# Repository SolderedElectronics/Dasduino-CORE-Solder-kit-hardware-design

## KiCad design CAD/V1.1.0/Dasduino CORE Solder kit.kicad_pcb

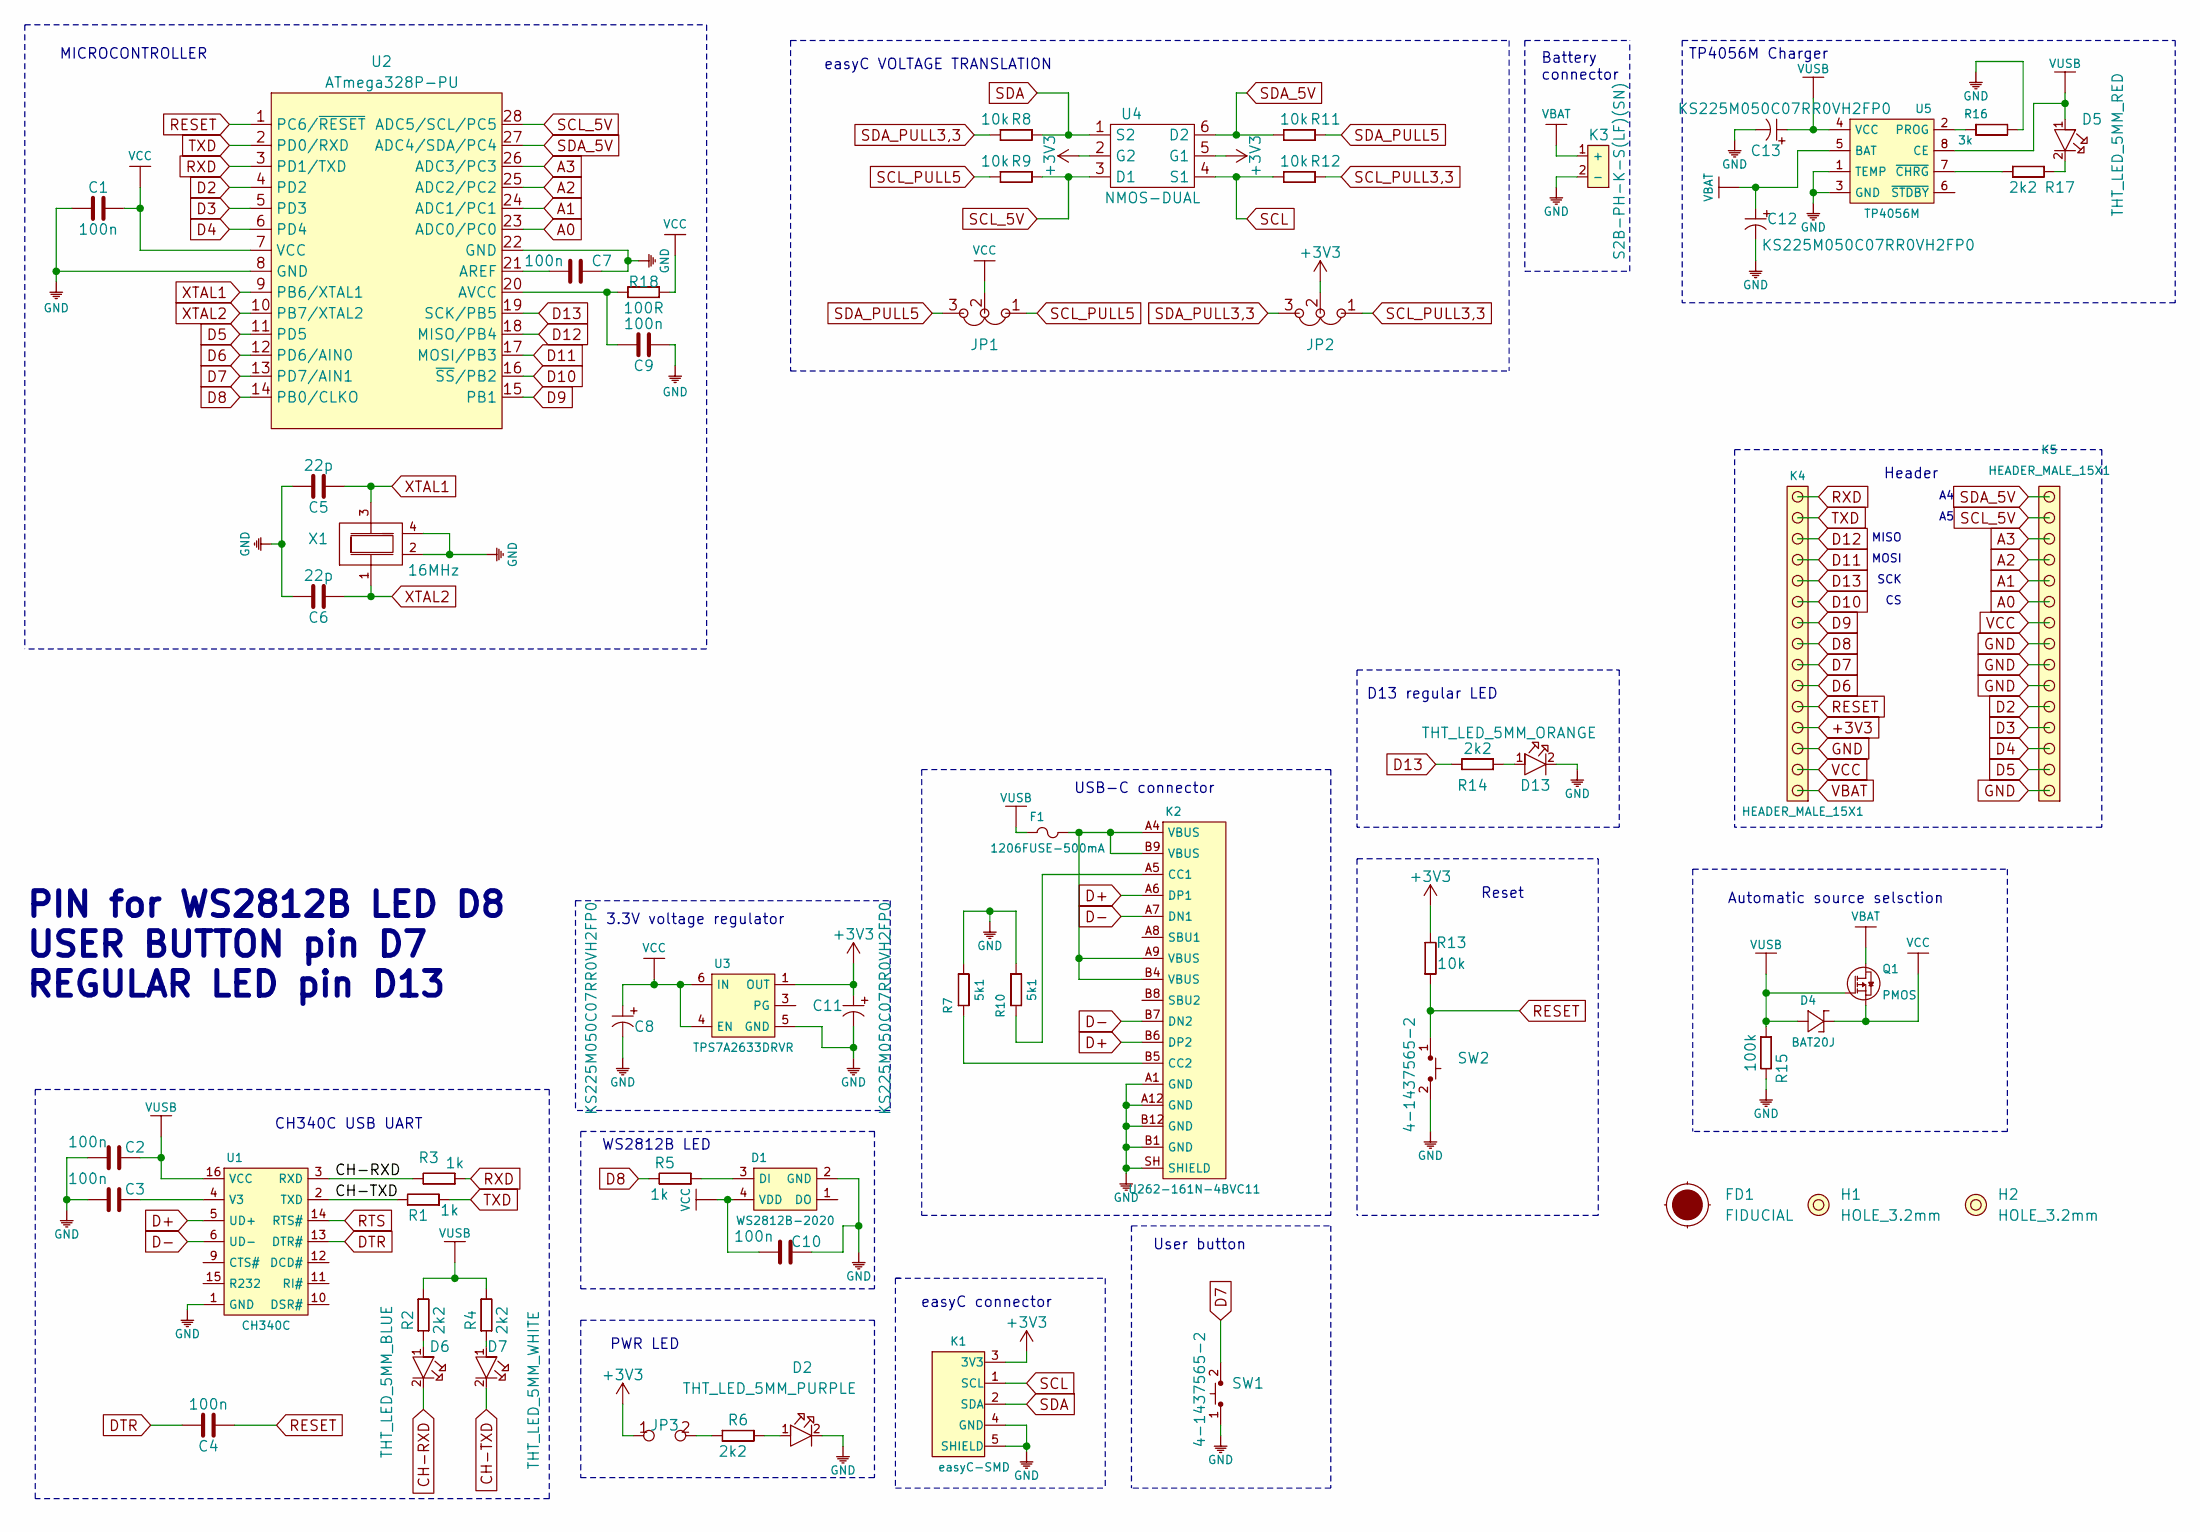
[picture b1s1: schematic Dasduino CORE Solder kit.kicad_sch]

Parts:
C1, C2, C3, C4, C7, C9, C10: 100n; C_Ceramic_THT_5mm
C5, C6: 22p; C_Ceramic_THT_5mm
C8, C11, C12, C13: KS225M050C07RR0VH2FP0
D1: WS2812B-2020
D2: THT_LED_5MM_PURPLE; THT LED 5mm PURPLE
D4: BAT20J; SOD-323
D5: THT_LED_5MM_RED; THT LED 5mm RED
D6: THT_LED_5MM_BLUE
D7: THT_LED_5MM_WHITE; THT LED 5mm WHITE
D13: THT_LED_5MM_ORANGE; THT LED 5mm ORANGE
F1: 1206FUSE-500mA; 1206FUSE
FD1: FIDUCIAL; FIDUCIAL_23
H1, H2: HOLE_3.2mm
JP1, JP2: SMD_JUMPER_3_PAD_TRACE
JP3: SMD_JUMPER
K1: easyC-SMD; easyC-connector
K2: U262-161N-4BVC11
K3: S2B-PH-K-S(LF)(SN)
K4, K5: HEADER_MALE_15X1
Q1: PMOS; SOT-23-3
R1, R3, R5: 1k; THT OTPORNIK
R2, R4, R6, R14, R17: 2k2; THT OTPORNIK
R7, R10: 5k1; 0603R
R8, R9, R11, R12, R13: 10k; THT OTPORNIK
R15: 100k; THT OTPORNIK
R16: 3k; 0603R
R18: 100R; THT OTPORNIK
SW1, SW2: 4-1437565-2
U1: CH340C; SOP-16
U2: ATmega328P-PU
U3: TPS7A2633DRVR
U4: NMOS-DUAL; SOT-363
U5: TP4056M; TP4056M-MSOP8
X1: 16MHz; CRYSTAL_3225__4_PAD

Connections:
+3V3: C11.1 (+), JP2.2, JP3.1, K1.3 (3V3), K4.4, R13.2, U3.1 (OUT), U4.2 (G2), U4.5 (G1)
A0: K5.10, U2.23 (ADC0/PC0)
A1: K5.11, U2.24 (ADC1/PC1)
A2: K5.12, U2.25 (ADC2/PC2)
A3: K5.13, U2.26 (ADC3/PC3)
CH-RXD: D6.2, R3.2, U1.3 (RXD)
CH-TXD: D7.2, R1.2, U1.2 (TXD)
D2: K5.5, U2.4 (PD2)
D3: K5.4, U2.5 (PD3)
D4: K5.3, U2.6 (PD4)
D5: K5.2, U2.11 (PD5)
D6: K4.6, U2.12 (PD6/AIN0)
D7: K4.7, SW1.2, U2.13 (PD7/AIN1)
D8: K4.8, R5.2, U2.14 (PB0/CLKO)
D9: K4.9, U2.15 (PB1)
D10: K4.10, U2.16 (~SS/PB2)
D11: K4.12, U2.17 (MOSI/PB3)
D12: K4.13, U2.18 (MISO/PB4)
D13: K4.11, R14.2, U2.19 (SCK/PB5)
D+: K2.A6 (DP1), K2.B6 (DP2), U1.5 (UD+)
D-: K2.A7 (DN1), K2.B7 (DN2), U1.6 (UD-)
DTR: C4.1, U1.13 (DTR#)
GND: C1.2, C2.1, C3.1, C5.1, C6.1, C7.2, C8.2 (-), C9.2, C10.2, C11.2 (-), C12.2 (-), C13.2 (-), D1.2 (GND), D2.2, D13.2, K1.4 (GND), K1.5 (SHIELD), K2.A1 (GND), K2.A12 (GND), K2.B1 (GND), K2.B12 (GND), K2.SH (SHIELD), K3.2 (-), K4.3, K5.1, K5.6, K5.7, K5.8, R7.2, R10.2, R15.2, R16.2, SW1.1, SW2.2, U1.1 (GND), U2.8 (GND), U2.22 (GND), U3.5 (GND), U5.1 (TEMP), U5.3 (GND), X1.2, X1.4
unnamed: C3.2, U1.4 (V3)
unnamed: C7.1, U2.21 (AREF)
unnamed: C9.1, R18.2, U2.20 (AVCC)
unnamed: D1.3 (DI), R5.1
unnamed: D2.1, R6.2
unnamed: D5.2, R17.2
unnamed: D6.1, R2.1
unnamed: D7.1, R4.1
unnamed: D13.1, R14.1
unnamed: F1.2, K2.A4 (VBUS), K2.A9 (VBUS), K2.B4 (VBUS), K2.B9 (VBUS)
unnamed: JP3.2, R6.1
unnamed: K2.A5 (CC1), R10.1
unnamed: K2.B5 (CC2), R7.1
unnamed: R16.1, U5.2 (PROG)
unnamed: R17.1, U5.7 (~CHRG)
RESET: C4.2, K4.5, R13.1, SW2.1, U2.1 (PC6/~RESET)
RTS: U1.14 (RTS#)
RXD: K4.15, R3.1, U2.3 (PD1/TXD)
SCL: K1.1 (SCL), R12.1, U4.4 (S1)
SCL_5V: K5.14, R9.2, U2.28 (ADC5/SCL/PC5), U4.3 (D1)
SCL_PULL3,3: JP2.1, R12.2
SCL_PULL5: JP1.1, R9.1
SDA: K1.2 (SDA), R8.2, U4.1 (S2)
SDA_5V: K5.15, R11.1, U2.27 (ADC4/SDA/PC4), U4.6 (D2)
SDA_PULL3,3: JP2.3, R8.1
SDA_PULL5: JP1.3, R11.2
TXD: K4.14, R1.1, U2.2 (PD0/RXD)
VBAT: C12.1 (+), K3.1 (+), K4.1, Q1.3 (D), U5.5 (BAT)
VCC: C1.1, C8.1 (+), C10.1, D1.4 (VDD), D4.2 (K), JP1.2, K4.2, K5.9, Q1.2 (S), R18.1, U2.7 (VCC), U3.4 (EN), U3.6 (IN)
VUSB: C2.2, C13.1 (+), D4.1 (A), D5.1, F1.1, Q1.1 (G), R2.2, R4.2, R15.1, U1.16 (VCC), U5.4 (VCC), U5.8 (CE)
XTAL1: C5.2, U2.9 (PB6/XTAL1), X1.3
XTAL2: C6.2, U2.10 (PB7/XTAL2), X1.1

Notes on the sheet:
TP4056M Charger
PIN for WS2812B LED D8 USER BUTTON pin D7 REGULAR LED pin D13
easyC connector
Automatic source selsction
Battery connector
USB-C connector
3.3V voltage regulator
easyC VOLTAGE TRANSLATION
MICROCONTROLLER
PWR LED
Header
Reset
CH340C USB UART
SCK
User button
WS2812B LED
D13 regular LED
MOSI
MISO

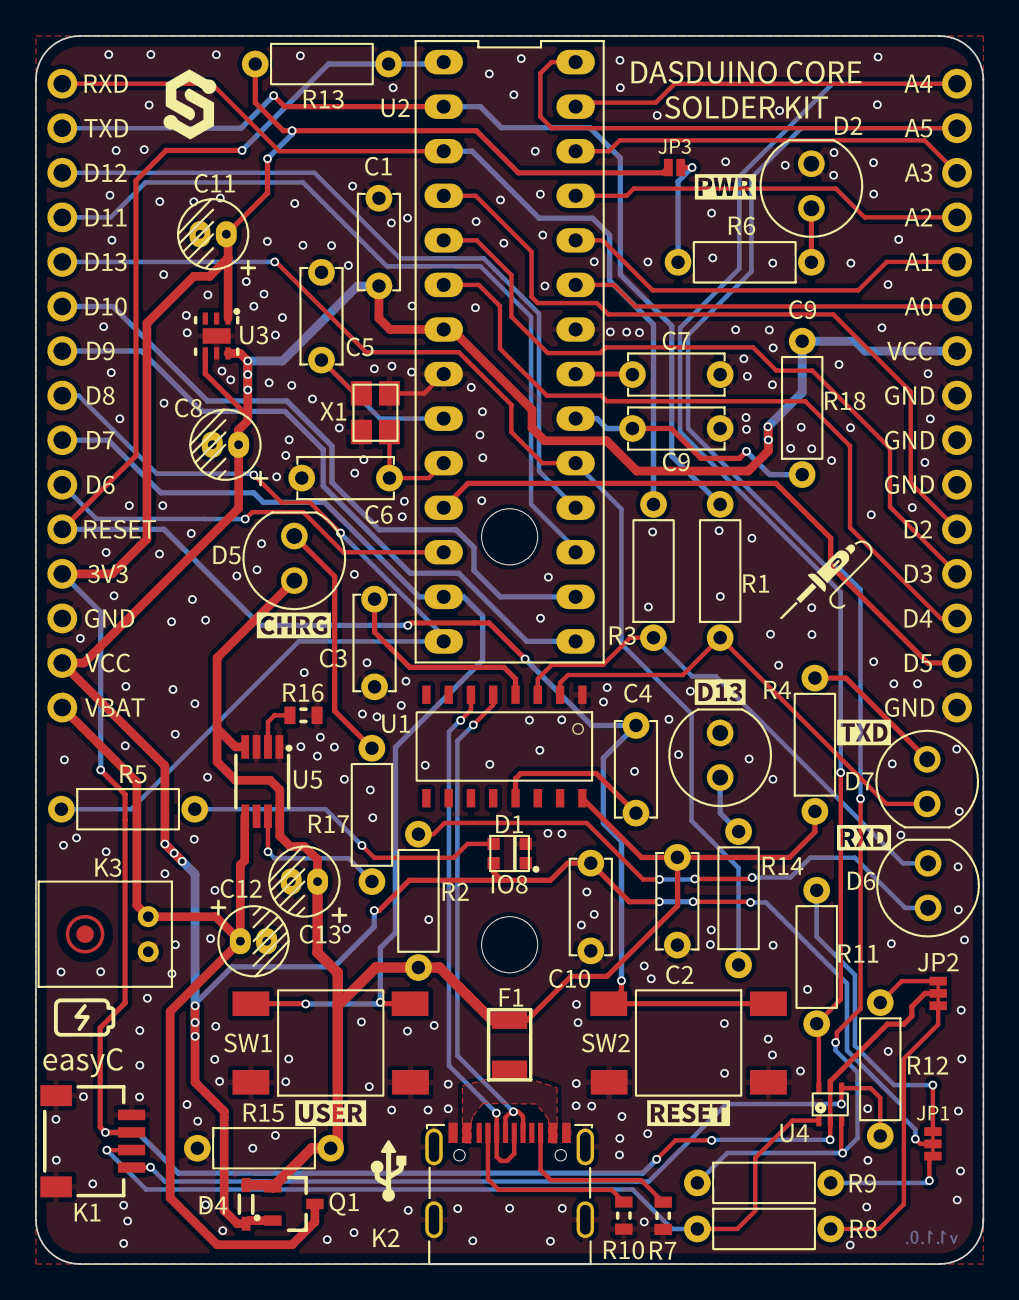
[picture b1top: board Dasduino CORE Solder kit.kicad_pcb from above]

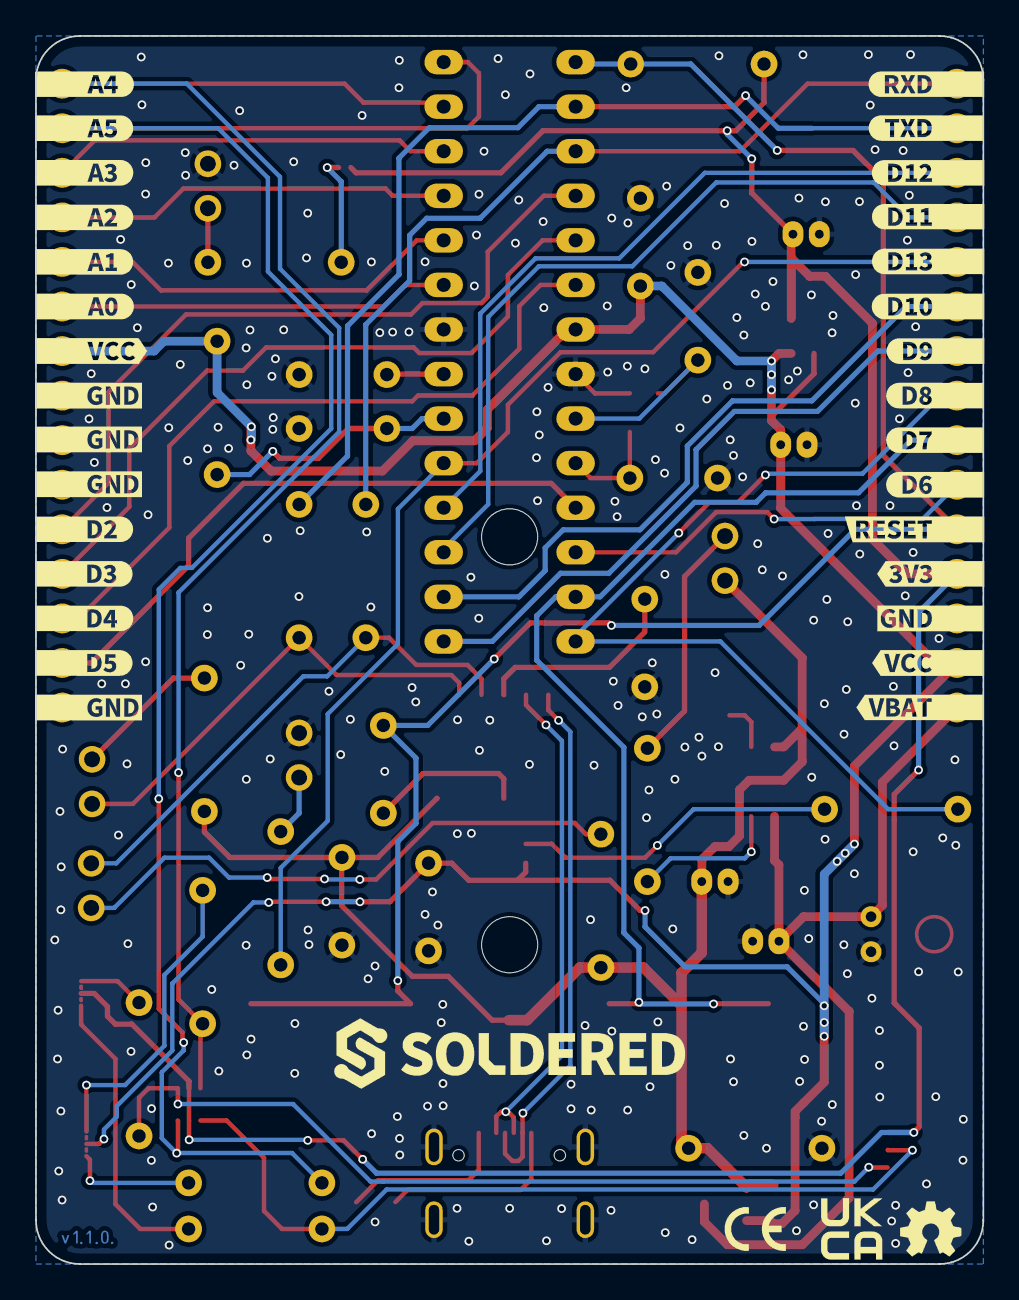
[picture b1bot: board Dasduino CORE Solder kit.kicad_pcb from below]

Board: 2 copper layers, 54.0 x 70.0 mm, 184 parts (31 on the bottom side), 54 nets.

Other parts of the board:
Ref**: Val**; Version1.1.0
kibuzzard-64AA48AA: G***; kibuzzard-64AA48AA
kibuzzard-64AA4247: G***; kibuzzard-64AA4247
kibuzzard-64AA4896: G***; kibuzzard-64AA4896
kibuzzard-64B67D4E: G***; kibuzzard-64B67D4E
kibuzzard-64B67D7C: G***; kibuzzard-64B67D7C
kibuzzard-64B67D8F: G***; kibuzzard-64B67D8F
kibuzzard-64B67DA4: G***; kibuzzard-64B67DA4
kibuzzard-64B67E8A: G***; kibuzzard-64B67E8A
kibuzzard-64B67E49: G***; kibuzzard-64B67E49
kibuzzard-64B67E67: G***; kibuzzard-64B67E67
kibuzzard-642BFB1A: G***; kibuzzard-642BFB1A
kibuzzard-642BFB2F: G***; kibuzzard-642BFB2F
kibuzzard-642BFB3D: G***; kibuzzard-642BFB3D
kibuzzard-642BFB4C: G***; kibuzzard-642BFB4C
kibuzzard-642BFB5B: G***; kibuzzard-642BFB5B
kibuzzard-642BFB8A: G***; kibuzzard-642BFB8A
kibuzzard-642BFB9E: G***; kibuzzard-642BFB9E
kibuzzard-642BFB12: G***; kibuzzard-642BFB12
kibuzzard-642BFB22: G***; kibuzzard-642BFB22
kibuzzard-642BFB29: G***; kibuzzard-642BFB29
kibuzzard-642BFB37: G***; kibuzzard-642BFB37
kibuzzard-642BFB46: G***; kibuzzard-642BFB46
kibuzzard-642BFB55: G***; kibuzzard-642BFB55
kibuzzard-642BFB62: G***; kibuzzard-642BFB62
kibuzzard-642BFB71: G***; kibuzzard-642BFB71
kibuzzard-642BFB77: G***; kibuzzard-642BFB77
kibuzzard-642BFB82: G***; kibuzzard-642BFB82
kibuzzard-642BFB91: G***; kibuzzard-642BFB91
kibuzzard-642BFBAC: G***; kibuzzard-642BFBAC
kibuzzard-642BFBB3: G***; kibuzzard-642BFBB3
kibuzzard-642BFC1D: G***; kibuzzard-642BFC1D
kibuzzard-642BFC5B: G***; kibuzzard-642BFC5B
kibuzzard-642BFC6E: G***; kibuzzard-642BFC6E
kibuzzard-642BFC7A: G***; kibuzzard-642BFC7A
kibuzzard-642BFC8B: G***; kibuzzard-642BFC8B
kibuzzard-642BFC26: G***; kibuzzard-642BFC26
kibuzzard-642BFC34: G***; kibuzzard-642BFC34
kibuzzard-642BFC61: G***; kibuzzard-642BFC61
kibuzzard-642BFC67: G***; kibuzzard-642BFC67
kibuzzard-642BFC82: G***; kibuzzard-642BFC82
kibuzzard-642BFC91: G***; kibuzzard-642BFC91
kibuzzard-642BFCA9: G***; kibuzzard-642BFCA9
kibuzzard-642BFCB2: G***; kibuzzard-642BFCB2
kibuzzard-642BFCBF: G***; kibuzzard-642BFCBF
kibuzzard-642BFCC5: G***; kibuzzard-642BFCC5
kibuzzard-642BFCCF: G***; kibuzzard-642BFCCF
kibuzzard-642BFCE4: G***; kibuzzard-642BFCE4
kibuzzard-642BFCFA: G***; kibuzzard-642BFCFA
kibuzzard-642BFD1A: G***; kibuzzard-642BFD1A
kibuzzard-642BFD07: G***; kibuzzard-642BFD07
kibuzzard-642BFD7D: G***; kibuzzard-642BFD7D
kibuzzard-642BFD8B: G***; kibuzzard-642BFD8B
kibuzzard-642BFD9A: G***; kibuzzard-642BFD9A
kibuzzard-642BFD20: G***; kibuzzard-642BFD20
kibuzzard-642BFD29: G***; kibuzzard-642BFD29
kibuzzard-642BFD72: G***; kibuzzard-642BFD72
kibuzzard-642BFD77: G***; kibuzzard-642BFD77
kibuzzard-642BFD85: G***; kibuzzard-642BFD85
kibuzzard-642BFD94: G***; kibuzzard-642BFD94
kibuzzard-642BFDA1: G***; kibuzzard-642BFDA1
kibuzzard-642BFDA8: G***; kibuzzard-642BFDA8
kibuzzard-642BFDAE: G***; kibuzzard-642BFDAE
kibuzzard-642BFDB5: G***; kibuzzard-642BFDB5
kibuzzard-642BFDBA: G***; kibuzzard-642BFDBA
kibuzzard-642BFDC3: G***; kibuzzard-642BFDC3
kibuzzard-642BFDC8: G***; kibuzzard-642BFDC8
kibuzzard-642BFDCE: G***; kibuzzard-642BFDCE
kibuzzard-642BFDD6: G***; kibuzzard-642BFDD6
kibuzzard-642BFDDD: G***; kibuzzard-642BFDDD
kibuzzard-642BFDE3: G***; kibuzzard-642BFDE3
kibuzzard-642BFDEA: G***; kibuzzard-642BFDEA
kibuzzard-642BFDF1: G***; kibuzzard-642BFDF1
kibuzzard-642BFDFC: G***; kibuzzard-642BFDFC
kibuzzard-642BFE0F: G***; kibuzzard-642BFE0F
kibuzzard-642BFE1C: G***; kibuzzard-642BFE1C
kibuzzard-642BFE03: G***; kibuzzard-642BFE03
kibuzzard-642BFE4E: G***; kibuzzard-642BFE4E
kibuzzard-642BFE5E: G***; kibuzzard-642BFE5E
kibuzzard-642BFE6D: G***; kibuzzard-642BFE6D
kibuzzard-642BFE7D: G***; kibuzzard-642BFE7D
kibuzzard-642BFE8B: G***; kibuzzard-642BFE8B
kibuzzard-642BFE09: G***; kibuzzard-642BFE09
kibuzzard-642BFE16: G***; kibuzzard-642BFE16
kibuzzard-642BFE28: G***; kibuzzard-642BFE28
kibuzzard-642BFE38: G***; kibuzzard-642BFE38
kibuzzard-642BFE57: G***; kibuzzard-642BFE57
kibuzzard-642BFE74: G***; kibuzzard-642BFE74
kibuzzard-642BFE84: G***; kibuzzard-642BFE84
kibuzzard-642BFE91: G***; kibuzzard-642BFE91
kibuzzard-642BFE97: G***; kibuzzard-642BFE97
kibuzzard-642BFEA7: G***; kibuzzard-642BFEA7
kibuzzard-642BFEAD: G***; kibuzzard-642BFEAD
kibuzzard-642BFEB3: G***; kibuzzard-642BFEB3
kibuzzard-642BFEBA: G***; kibuzzard-642BFEBA
kibuzzard-642C00A8: G***; kibuzzard-642C00A8
kibuzzard-642C00B7: G***; kibuzzard-642C00B7
kibuzzard-642C00C3: G***; kibuzzard-642C00C3
kibuzzard-642C00CF: G***; kibuzzard-642C00CF
kibuzzard-642C00D7: G***; kibuzzard-642C00D7
kibuzzard-642C00E2: G***; kibuzzard-642C00E2
kibuzzard-642C00EB: G***; kibuzzard-642C00EB
kibuzzard-642C00F1: G***; kibuzzard-642C00F1
kibuzzard-642C00FA: G***; kibuzzard-642C00FA
kibuzzard-642C01B2: G***; kibuzzard-642C01B2
kibuzzard-642C01BA: G***; kibuzzard-642C01BA
kibuzzard-642C01C6: G***; kibuzzard-642C01C6
kibuzzard-642C01EF: G***; kibuzzard-642C01EF
kibuzzard-642C005E: G***; kibuzzard-642C005E
kibuzzard-642C006A: G***; kibuzzard-642C006A
kibuzzard-642C008F: G***; kibuzzard-642C008F
kibuzzard-642C014C: G***; kibuzzard-642C014C
kibuzzard-642C016D: G***; kibuzzard-642C016D
kibuzzard-642C017E: G***; kibuzzard-642C017E
kibuzzard-642C018B: G***; kibuzzard-642C018B
kibuzzard-642C0029: G***; kibuzzard-642C0029
kibuzzard-642C0045: G***; kibuzzard-642C0045
kibuzzard-642C0052: G***; kibuzzard-642C0052
kibuzzard-642C0126: G***; kibuzzard-642C0126
kibuzzard-642C0138: G***; kibuzzard-642C0138
kibuzzard-642C0140: G***; kibuzzard-642C0140
kibuzzard-642C0156: G***; kibuzzard-642C0156
kibuzzard-642C0160: G***; kibuzzard-642C0160
kibuzzard-642C0177: G***; kibuzzard-642C0177
kibuzzard-642C0192: G***; kibuzzard-642C0192

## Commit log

2022-08-06 Updating open source files.
